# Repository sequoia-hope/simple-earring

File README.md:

# simple_earring

Co-designed LED earring: a Ø30.5 mm teardrop, 4-layer board with an RP2350A and external QSPI
flash in the middle and 45 RGB LEDs on two rings round it (37 on the outer ring, 8 inside). It runs
from a small LiPo cell (LPR302823) on the back and charges over USB-C. One button does both power
(a soft latch) and BOOTSEL. There is also an IMU, an ambient light sensor and a generated TPU clip-on
case. JLCPCB rules, all parts from LCSC.

The current board (rev 3, variant A) uses 45 WS2816C-1313 addressable pixels split into three
switched zones. Variants B–F study a cheaper build that drives plain RGB LEDs (XL-1615) from a
matrix driver (AW20198QNR), about $3 less per board. It routes on 6 layers; 4 layers is down to a few
open connections.

**Project page: <https://sequoia-hope.github.io/simple-earring/>**: every design variant (A, the
routed WS2816C board, and the B–F matrix-driver study) with board previews, a comparison table, the
interactive viewer (schematic, PCB layers, 3D) and the design notes. It is the local dashboard
(`proj up simple_earring`), published with `scripts/publish_pages.py --push`.

The design is *generated*: edit `design.yaml` (shape, LED count, sizes) and
`scripts/circuit.py` (netlist), then rebuild.

**Status:** rev 1 (SK6805-EC10 LEDs, 2032 coin cell) was ordered, assembled and works. It lives in a
separate worktree at `~/pcb/simple_earring_shipped` (commit `43eadc1`). This tree is rev 3: variant A
is routed with ultraroute to 0 DRC errors / 0 unconnected and has passed gate 7. The matrix variants
are placed; the 4- or 6-layer decision for them is open. See `docs/PLAN.md` for the plan of record
and the project page's feed for the narrative.

## Pipeline

```
python3 build.py                # full: board -> place -> route -> drc -> render -> export
python3 build.py --to place     # stop after a stage (board|place|route|drc|render|export)
```

Stages (each is also runnable standalone from `scripts/`):

| stage  | script              | what it does                                        |
|--------|---------------------|-----------------------------------------------------|
| board  | `gen_board.py`      | netlist from `circuit.py` -> fresh 4-layer .kicad_pcb, outline, nets |
| place  | `place.py`          | LED ring, MCU cluster front, holder back, USB at edge |
| route  | `route.py`          | locked pre-routes + pours, then ultraroute for the rest, zone fills |
| drc    | `drc.py`            | kicad-cli DRC, parsed pass/fail report              |
| render | `render.py`         | renders, layer PNGs, GLB, and the `out/` dashboard  |
| export | `export.py`         | JLCPCB gerbers/drill + BOM/CPL from LCSC numbers    |

The KiCad project is `hw/earring/a/earring.kicad_*` (the Boardroom suite's
`hw/<board>/<variant>/` layout; `scripts/paths.py` owns the locations). Build products
land in `out/` (renders, dashboard, `drc.json`, `production/`, `jlcpcb/`).

The dashboard's design gallery reads `design/variants.toml` (card text) and `pcbview.toml` (the
boards); rebuild the viewer with `scripts/view.sh build pcbview.toml`, rewrite the page with
`python3 scripts/render.py --index-only`, then publish it to GitHub Pages (the `gh-pages` branch)
with `python3 scripts/publish_pages.py --push`.

## Boardroom suite

This is a Boardroom project (`~/Software/easy_pcb`): `design/status.json` is its
headline state, `.claude/skills/pcb-design/` the vendored skill, `pcbview.toml` the
viewer config. `compose/earring/` is Circuit Composer's view of the circuit
(generated by `scripts/export_compose.py`, build stage `compose`), and
`route/earring/recipe.json` is the ultraroute recipe behind the installed route.
Routing is ultraroute: the `route` stage runs the pinned `vendor/ultraroute`
(`git submodule update --init`; `scripts/route.sh` builds it, needs Rust) with that recipe.
Alongside the board pipeline: `gen_schematic.py` (readable schematic + PDF),
`gen_case.py` (TPU case STLs/STEP), `firmware/` (PlatformIO, arduino-pico), and
`tools/` (bench instruments — charge monitor, placement spot scanner).

## Dashboard

```
cd out && python3 -m http.server 8618 --bind 0.0.0.0
```

`out/index.html` is a reverse-chronological update feed over the live build
outputs: renders, the copper-layer stack viewer, the 3D board, the schematic,
the case preview and the bench pages. It is **generated by `scripts/render.py`**
(the `FEED` list at the top of that file) — hand edits to the served page are
wiped by the next build. `python3 scripts/render.py --index-only` rewrites just
the page.

## Sources of truth

- `design.yaml` — geometry + rules parameters
- `scripts/circuit.py` — components and nets (references `bom/parts.yaml`)
- `bom/parts.yaml` — every part with LCSC number + footprint
- `library/parts.pretty/` — local footprints (proven ones lifted from prior boards)
- `docs/PLAN.md` — plan of record: current state, open work, hard-won constraints

## Provenance

Footprints and circuit patterns reuse the proven `earring` (RP2040 + LGS4056H + USB-C)
and `rp2350-pendant` (RP2350 QFN-60, 1010 LED ring) projects.

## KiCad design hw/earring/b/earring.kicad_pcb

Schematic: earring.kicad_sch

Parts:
BT1: LPR302823; BAT_LPR302823_PADS
C1, C2, C3, C4, C5, C6, C7, C8, C9, C21, C23, C24, C25, C26, C27, C28, C77, C81, C83, C85, C87: 100n; C_0402_1005Metric
C11, C12, C13, C22: 4.7u; C_0402_1005Metric_small_pads
C14, C15: 15p; C_0402_1005Metric
C16, C17, C29, C75, C86: 10u; C_0603_1608Metric
C18, C19, C80, C82, C84: 1u; C_0402_1005Metric
C76: 10n; C_0402_1005Metric
D2: BAV99W; SOT-323_BAT54SW
D3: 1N4007WS; D_SOD-323
D4: BAV70W; SOT-323_BAT54SW
D5: 1N4148WS; D_SOD-323
D6: PESD5V0S1BL; D_SOD-882
J1: USB-C; USB-C_SMD-TYPE-C-31-M-12_1
L1: 3.3uH; L_pol_2016
LED1, LED2, LED3, LED4, LED5, LED6, LED7, LED8, LED9, LED10, LED11, LED12, LED13, LED14, LED15, LED16, LED17, LED18, LED19, LED20, LED21, LED22, LED23, LED24, LED25, LED26, LED27, LED28, LED29, LED30, LED31, LED32, LED33, LED34, LED35, LED36, LED37, LED38, LED39, LED40, LED41, LED42, LED43, LED44, LED45: XL-1010RGB; LED_XL-1010RGB
Q1: ALS-PT19; SENSOR_ALS-PT19
Q2, Q8: CJ2101; SOT-323_MOSFET
Q4: LBSS84WT1G; SOT-323_MOSFET
Q5, Q6, Q7: BSS138W; SOT-323_MOSFET
R1, R3, R30: 1k; R_0402_1005Metric
R2, R19, R20, R22: 10k; R_0402_1005Metric
R4, R5: 5.1k; R_0402_1005Metric
R6, R7: 27; R_0402_1005Metric
R8: 18k; R_0402_1005Metric
R11, R12, R21, R29: 1M; R_0402_1005Metric
R13: 33; R_0402_1005Metric
R14, R15, R27, R38, R39: 4.7k; R_0402_1005Metric
R16: 22k; R_0402_1005Metric
R17, R18, R24, R25, R26, R36, R37: 100k; R_0402_1005Metric
R28: 680k; R_0402_1005Metric
R35: 47k; R_0402_1005Metric
SW2: PWR; SW_B3U-3000P
TP1: RUN; TestPoint_Pad_1.5x1.5mm
TP2: SWCLK; TestPoint_Pad_1.5x1.5mm
TP3: SWDIO; TestPoint_Pad_1.5x1.5mm
U1: RP2350A; RP2350-QFN-60-1EP_7x7_P0.4mm_EP3.4x3.4mm_ThermalVias
U2: LGS4056H; DFN-8-1EP_2x2mm_P0.5mm_EP0.9x1.5mm
U3: NCP730-3.3; WDFN-6-2x2
U5: USBLC6-2P6; SOT-666
U6: LSM6DS3TR-C; LGA-14_L3.0-W2.5-P0.50-TL
U7: W25Q16JVUXIQ; USON-8_L3.0-W2.0-P0.50-BL-EP
U8: 74LVC2G14; SOT-363_SC-70-6
U11: IS31FL3741A; QFN-60-1EP_7x7mm_P0.4mm_EP5.4x5.4mm
Y1: 12MHz; Crystal_SMD_3225-4Pin_3.2x2.5mm_ABM8

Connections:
3V3: C1.1, C2.1, C3.1, C4.1, C7.1, C8.1, C9.1, C11.1, C19.1, C23.1, C24.1, C25.1, C77.1, Q1.1 (C), Q8.2 (S), R2.2, R13.1, R14.2, R15.2, R26.1, R37.2, R38.2, R39.2, U1.1 (IOVDD), U1.11 (IOVDD), U1.20 (IOVDD), U1.30 (IOVDD), U1.38 (IOVDD), U1.44 (ADC_AVDD), U1.45 (IOVDD), U1.49 (VREG_VIN), U1.53 (USB_OTP_VDD), U1.54 (QSPI_IOVDD), U3.1 (OUT), U6.2 (SDx), U6.3 (SCx), U6.5 (VDDIO), U6.8 (VDD), U6.12 (CS), U7.8 (VCC), U8.5 (VCC)
BOOTSEL: R3.1, U1.60 (QSPI_SS), U7.1 (/CS)
BOOTSEL_SW: Q7.3 (D), R3.2
BOOT_TMR: C75.1, D5.2 (A), R28.2, U8.1 (1A)
BTN_EXT: D6.1, R30.1, SW2.2
BTN_N: C27.1, D4.3 (K), R30.2
BTN_SENSE: D5.1 (K), Q8.3 (D), R27.1, R28.1, U1.33 (GPIO21)
CC1: J1.A5 (CC1), R4.1
CC2: J1.B5 (CC2), R5.1
CHRG: U1.31 (GPIO19), U2.7 (CHRG)
CHRG_DONE: U1.42 (GPIO28), U2.6 (DONE)
CS1: LED1.1 (R), LED2.1 (R), LED3.1 (R), LED4.1 (R), LED5.1 (R), LED6.1 (R), LED7.1 (R), LED8.1 (R), LED9.1 (R), U11.26 (CS1)
CS2: LED1.2 (G), LED2.2 (G), LED3.2 (G), LED4.2 (G), LED5.2 (G), LED6.2 (G), LED7.2 (G), LED8.2 (G), LED9.2 (G), U11.27 (CS2)
CS3: LED1.4 (B), LED2.4 (B), LED3.4 (B), LED4.4 (B), LED5.4 (B), LED6.4 (B), LED7.4 (B), LED8.4 (B), LED9.4 (B), U11.28 (CS3)
CS4: LED10.1 (R), LED11.1 (R), LED12.1 (R), LED13.1 (R), LED14.1 (R), LED15.1 (R), LED16.1 (R), LED17.1 (R), LED18.1 (R), U11.29 (CS4)
CS5: LED10.2 (G), LED11.2 (G), LED12.2 (G), LED13.2 (G), LED14.2 (G), LED15.2 (G), LED16.2 (G), LED17.2 (G), LED18.2 (G), U11.30 (CS5)
CS6: LED10.4 (B), LED11.4 (B), LED12.4 (B), LED13.4 (B), LED14.4 (B), LED15.4 (B), LED16.4 (B), LED17.4 (B), LED18.4 (B), U11.31 (CS6)
CS7: LED19.1 (R), LED20.1 (R), LED21.1 (R), LED22.1 (R), LED23.1 (R), LED24.1 (R), LED25.1 (R), LED26.1 (R), LED27.1 (R), U11.32 (CS7)
CS8: LED19.2 (G), LED20.2 (G), LED21.2 (G), LED22.2 (G), LED23.2 (G), LED24.2 (G), LED25.2 (G), LED26.2 (G), LED27.2 (G), U11.33 (CS8)
CS9: LED19.4 (B), LED20.4 (B), LED21.4 (B), LED22.4 (B), LED23.4 (B), LED24.4 (B), LED25.4 (B), LED26.4 (B), LED27.4 (B), U11.34 (CS9)
CS10: LED28.1 (R), LED29.1 (R), LED30.1 (R), LED31.1 (R), LED32.1 (R), LED33.1 (R), LED34.1 (R), LED35.1 (R), LED36.1 (R), U11.35 (CS10)
CS11: LED28.2 (G), LED29.2 (G), LED30.2 (G), LED31.2 (G), LED32.2 (G), LED33.2 (G), LED34.2 (G), LED35.2 (G), LED36.2 (G), U11.37 (CS11)
CS12: LED28.4 (B), LED29.4 (B), LED30.4 (B), LED31.4 (B), LED32.4 (B), LED33.4 (B), LED34.4 (B), LED35.4 (B), LED36.4 (B), U11.38 (CS12)
CS13: LED37.1 (R), LED38.1 (R), LED39.1 (R), LED40.1 (R), LED41.1 (R), LED42.1 (R), LED43.1 (R), LED44.1 (R), LED45.1 (R), U11.39 (CS13)
CS14: LED37.2 (G), LED38.2 (G), LED39.2 (G), LED40.2 (G), LED41.2 (G), LED42.2 (G), LED43.2 (G), LED44.2 (G), LED45.2 (G), U11.40 (CS14)
CS15: LED37.4 (B), LED38.4 (B), LED39.4 (B), LED40.4 (B), LED41.4 (B), LED42.4 (B), LED43.4 (B), LED44.4 (B), LED45.4 (B), U11.41 (CS15)
DRV_INTB: R37.1, U1.3 (GPIO1), U11.7 (INTB)
DRV_ISET: R35.1, U11.13 (ISET)
DRV_SCL: R39.1, U1.28 (GPIO17), U11.10 (SCL)
DRV_SDA: R38.1, U1.27 (GPIO16), U11.9 (SDA)
DRV_SDB: C87.1, R36.1, U1.29 (GPIO18), U11.11 (SDB)
GND: BT1.2 (-), C1.2, C2.2, C3.2, C4.2, C5.2, C6.2, C7.2, C8.2, C9.2, C11.2, C12.2, C13.2, C14.2, C15.2, C16.2, C17.2, C18.2, C19.2, C21.2, C22.2, C23.2, C24.2, C25.2, C26.2, C27.2, C28.2, C29.2, C75.2, C77.2, C80.2, C81.2, C82.2, C83.2, C84.2, C85.2, C86.2, C87.2, D6.2, J1.1 (SHLD), J1.2 (SHLD), J1.3 (SHLD), J1.4 (SHLD), J1.A1B12 (GND), J1.B1A12 (GND), Q5.2 (S), Q6.2 (S), Q7.2 (S), R4.2, R5.2, R8.2, R12.2, R16.2, R17.2, R20.2, R21.2, R25.2, R27.2, R29.2, R35.2, R36.2, SW2.1, U1.47 (VREG_PGND), U1.61 (GND(EP)), U2.1 (TEMP), U2.3 (GND), U2.9 (GND(EP)), U3.3 (GND), U3.EP, U5.2 (GND), U6.1 (SDO/SA0), U6.6 (GND), U6.7 (GND), U7.4 (GND), U7.9 (GND(EP)), U8.2 (GND), U11.8 (ADDR), U11.12 (GND), U11.36 (GND), U11.55 (GND), U11.61 (GND(EP)), Y1.2, Y1.4
IMU_INT1: U1.12 (GPIO8), U6.4 (INT1)
IMU_SCL: R15.1, U1.15 (GPIO11), U6.13 (SCL)
IMU_SDA: R14.1, U1.9 (GPIO6), U6.14 (SDA)
LATCH_G: D4.2 (A2), Q4.1 (G), Q5.3 (D), R24.2
LIGHT: C26.1, Q1.2 (E), R16.1, U1.40 (GPIO26/ADC0)
LONG: C76.1, Q7.1 (G), U8.4 (2Y)
LONG_N: U8.3 (2A), U8.6 (1Y)
PATH_GATE: Q2.1 (G), R21.1, R22.2
PRESS_N: D4.1 (A1), Q8.1 (G), R26.2
PROG: R8.1, U2.2 (PROG)
PWR_EN: D2.3 (K1A2), R17.1, R18.2, U3.4 (EN)
PWR_HOLD: Q5.1 (G), R25.1, U1.32 (GPIO20)
QSPI_SCLK: U1.56 (QSPI_SCLK), U7.6 (CLK)
QSPI_SD0: U1.57 (QSPI_SD0), U7.5 (DI/IO0)
QSPI_SD1: U1.59 (QSPI_SD1), U7.2 (DO/IO1)
QSPI_SD2: U1.58 (QSPI_SD2), U7.3 (/WP/IO2)
QSPI_SD3: U1.55 (QSPI_SD3), U7.7 (/HOLD/IO3)
RUN: Q6.3 (D), R2.1, TP1.1, U1.26 (RUN)
RUN_KICK: C76.2, Q6.1 (G), R29.1
SW1: LED1.3 (A), LED10.3 (A), LED19.3 (A), LED28.3 (A), LED37.3 (A), U11.16 (SW1)
SW2: LED2.3 (A), LED11.3 (A), LED20.3 (A), LED29.3 (A), LED38.3 (A), U11.17 (SW2)
SW3: LED3.3 (A), LED12.3 (A), LED21.3 (A), LED30.3 (A), LED39.3 (A), U11.18 (SW3)
SW4: LED4.3 (A), LED13.3 (A), LED22.3 (A), LED31.3 (A), LED40.3 (A), U11.19 (SW4)
SW5: LED5.3 (A), LED14.3 (A), LED23.3 (A), LED32.3 (A), LED41.3 (A), U11.20 (SW5)
SW6: LED6.3 (A), LED15.3 (A), LED24.3 (A), LED33.3 (A), LED42.3 (A), U11.21 (SW6)
SW7: LED7.3 (A), LED16.3 (A), LED25.3 (A), LED34.3 (A), LED43.3 (A), U11.22 (SW7)
SW8: LED8.3 (A), LED17.3 (A), LED26.3 (A), LED35.3 (A), LED44.3 (A), U11.23 (SW8)
SW9: LED9.3 (A), LED18.3 (A), LED27.3 (A), LED36.3 (A), LED45.3 (A), U11.24 (SW9)
SWCLK: TP2.1, U1.24 (SWCLK)
SWDIO: TP3.1, U1.25 (SWDIO)
SW_ON: D2.1 (A1), Q4.3 (D), R11.1
USB_C_DN: J1.A7 (D-), J1.B7 (D-), R7.1, U5.3 (IO2), U5.4 (IO2)
USB_C_DP: J1.A6 (D+), J1.B6 (D+), R6.1, U5.1 (IO1), U5.6 (IO1)
USB_DM: R7.2, U1.51 (USB_DM)
USB_DP: R6.2, U1.52 (USB_DP)
VBATT: BT1.1 (+), C17.1, D2.2 (K2), Q2.3 (D), Q4.2 (S), R24.1, U2.5 (BAT)
VBSENSE: C21.1, R11.2, R12.1, U1.43 (GPIO29/ADC3)
VBUS: C16.1, C28.1, D3.2 (A), J1.A4B9 (VBUS), J1.B4A9 (VBUS), R18.1, R19.1, R22.1, U2.4 (VCC), U2.8 (CE), U5.5 (VBUS)
VBUS_SENSE: R19.2, R20.1, U1.41 (GPIO27)
VDD_CORE: C5.1, C6.1, C12.1, C13.1, L1.1, U1.6 (DVDD), U1.23 (DVDD), U1.39 (DVDD), U1.50 (VREG_FB)
VREG_AVDD: C22.1, R13.2, U1.46 (VREG_AVDD)
VREG_LX: L1.2, U1.48 (VREG_LX)
VSYS: C18.1, C29.1, C80.1, C81.1, C82.1, C83.1, C84.1, C85.1, C86.1, D3.1 (K), Q2.2 (S), U3.6 (IN), U11.14 (AVCC), U11.15 (PVCC), U11.25 (PVCC)
XIN: C14.1, U1.21 (XIN), Y1.1
XOUT: R1.2, U1.22 (XOUT)
XTAL_R: C15.1, R1.1, Y1.3

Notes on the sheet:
simple_earring — generated schematic
143 components / 78 nets / 4-layer JLCPCB stackup. Power rails (GND, 3V3, VBATT, VSYS, VLED, VBUS, VDD_CORE) are power symbols; only cross-block signals use global labels. Generated from scripts/circuit.py — do not hand-edit; rebuild with `python3 build.py --only schematic`.
J1 is a TYPE-C-31-M-12 right-angle receptacle. VBUS charges the cell AND (rev 2) runs
the board through D3 -> VSYS while a cable is in — see the power-path block.
USB-C receptacle / ESD / series R
CHRG / DONE are open-drain -> GPIO with internal pull-up (low = active); software owns the charge indicator.
Li-ion charger (LGS4056H, 50mA) + LPR302823 LiPo
1M:1M divider off SW_ON, the power latch's output
(VBATT while the latch is held or the button is
pressed). Latch ON: VBATT/2 battery telemetry. Latch
OFF + USB: reads 0, telling firmware to show charge
status instead of running the show. GPIO29/ADC3.
Latch / battery sense -> ADC
3V3 LDO — EN = power latch OR USB (diode-OR, clamped)
Rev 2: USB boots the board even with the latch off. Against
R17's pulldown EN sits at ~VBUS/2, and D2's second diode
clamps it to VBATT+Vf (NCP730 abs max V_EN is VIN+0.3, even
during precharge of a dead cell). Firmware then sees
SW_ON=0 on the sense divider and shows charge status
instead of running the show.
USB wake — VBUS feeds EN through R18
Press: BTN_N -> GND pulls LATCH_G low through D4 A2, Q4 turns on,
SW_ON = VBATT enables the LDO through D2. The CPU then drives
PWR_HOLD high so Q5 keeps LATCH_G low after release. Long press:
firmware drops PWR_HOLD and power falls when the button is
released. D4 A1 pulls PRESS_N low while pressed (the one-button
block turns that into BTN_SENSE). With the board off BTN_N sits
near VBATT and PRESS_N at 0V, so A1 is reverse-biased. D4 is
SILICON (BAV70W), not Schottky: the off-state leaks x R24 must
stay under Q4's 0.45V minimum threshold even hot. ESD: D6 clamps
a strike at the pad and R30 keeps it off BTN_N/D4; C27 debounces.
power button + soft latch
Hold the power button: BTN_SENSE goes high (Q8), C75 charges through R28 and U8 trips 2.2-10.3s later (5s typ; spread
is U8's VT+ and C75's X5R tolerance/bias, simulated in design/sim/button). LONG straps QSPI_SS low through Q7/R3 for as
long as the button is held and kicks RUN low for ~10ms (C76/R29 -> Q6): the chip resets into BOOTSEL. Flash is not
touched. On battery the reset drops PWR_HOLD, so the board turns off on release: the force-off for hung firmware. D5
empties C75 on release. Firmware: GPIO21 no pull-up, high = held; long-press-off < 2s.
one button: long hold = BOOTSEL / force-off
Rev 2: VBATT is the cell alone, VSYS runs the board, so the charger's whole 41mA reaches the cell in
either switch position. Q2's SOURCE is VSYS and its drain VBATT — a P-FET body diode conducts

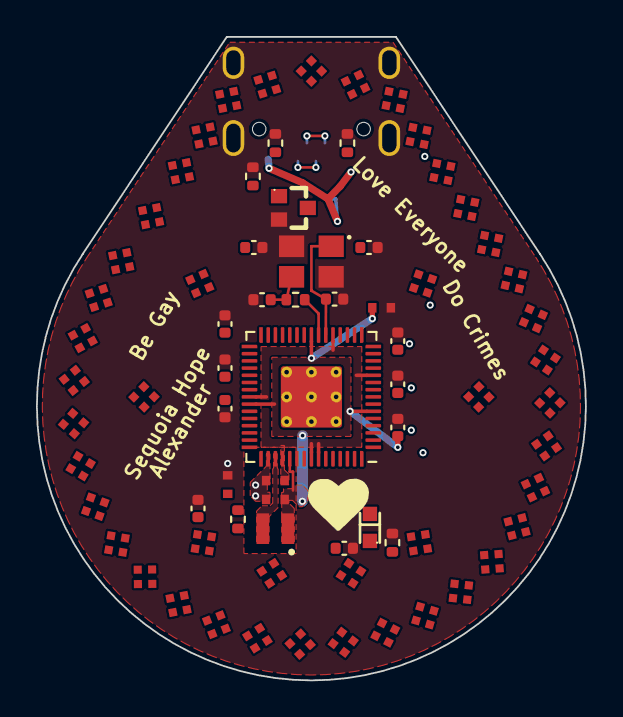
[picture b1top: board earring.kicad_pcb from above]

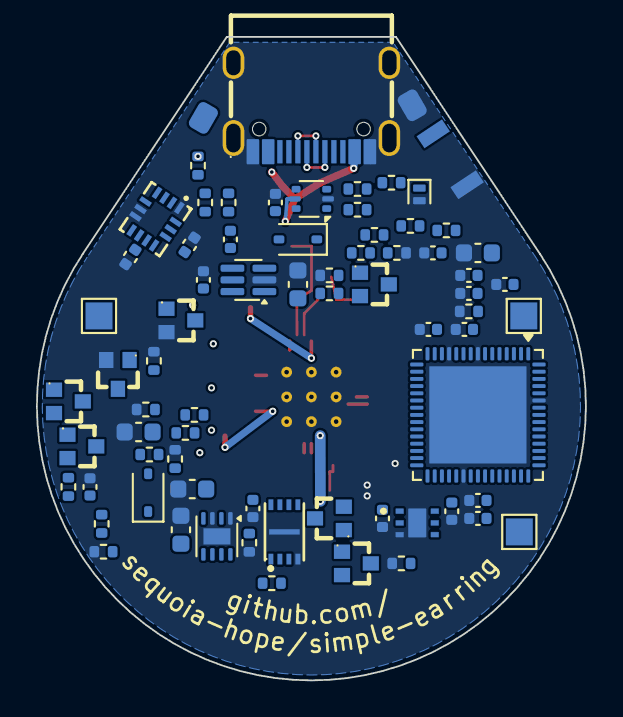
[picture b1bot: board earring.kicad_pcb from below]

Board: 6 copper layers, 30.5 x 35.8 mm, 143 parts (71 on the bottom side), 78 nets.

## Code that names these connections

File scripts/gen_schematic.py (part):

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        R = list(sides.get("r", []))
        T = list(sides.get("t", []))
        B = list(sides.get("b", []))
        # Top/bottom pin names run vertically INSIDE the box and would be
        # written straight through any side-pin name whose text reaches the
        # same columns. Where they would collide, reserve as many side slots
        # as the vertical name is tall so the two never share a row.
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            ys = [p[1] for p in pts]
            if max(ys) - min(ys) >= max(xs) - min(xs):
                # pins stack vertically -> park the text alongside the body,
                # between the two pins so it cannot reach either run
                rx, ry, rj = x + hw + 0.6, y - 2.0, "left bottom"
                vx, vy, vj = x + hw + 0.6, y + 1.1, "left bottom"
            else:
                # pins run left-right -> stack the text above and below,
                # stepped off the pin axis so it clears the wires' corners
                rx, ry, rj = x + 1.9, y - hh - 2.8, "left bottom"
                vx, vy, vj = x + 1.9, y + hh + 4.2, "left bottom"
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    def label(self, net, p, rot=0, just="left", size=1.0):
        """Name a wire that KiCad would otherwise auto-name.

        These are GLOBAL labels even though the run is local, because a
        plain label on the root sheet comes back out of the netlister as
        `/LED_D7`, and the board is matched to circuit.py by net name — a
        rename would relabel every net on a hand-routed board. Drawn small,
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# ---------------------------------------------------------------------------
def mcu_sides():
    gp = {g: p for g, p in GPIO.items()}
    used = {29: "GPIO18", 28: "GPIO17", 27: "GPIO16", 3: "GPIO1", 2: "GPIO0",
            34: "GPIO22", 9: "GPIO6", 15: "GPIO11", 12: "GPIO8",
            31: "GPIO19", 32: "GPIO20", 33: "GPIO21", 42: "GPIO28",
            40: "GPIO26/ADC0", 43: "GPIO29/ADC3"}
    unused = [(gp[g], f"GPIO{g}") for g in sorted(gp)
              if gp[g] not in used and gp[g] != 43]
    # Side pins are grouped by the block they wire to, with the gaps sized so
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            + [(21, "XIN"), (22, "XOUT")]
            + [None] * 8
            + [(51, "USB_DM"), (52, "USB_DP")])
    right = [(29, "GPIO18"), (28, "GPIO17"), (27, "GPIO16"), (3, "GPIO1"),
             (2, "GPIO0"), (34, "GPIO22"), (9, "GPIO6"), (15, "GPIO11"),
             (12, "GPIO8"), (31, "GPIO19"), (32, "GPIO20"), (33, "GPIO21"),
             (42, "GPIO28"),
             (40, "GPIO26/ADC0"), (43, "GPIO29/ADC3")]
    top = [(1, "IOVDD"), (11, "IOVDD"), (20, "IOVDD"), (30, "IOVDD"),
           (38, "IOVDD"), (45, "IOVDD"), (54, "QSPI_IOVDD"),
           (53, "USB_OTP_VDD"), (44, "ADC_AVDD"), None,
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    "rgb_led_1615": {"t": [("2", "A")],
                     "b": [("1", "R"), ("3", "G"), ("4", "B")]},
    # 74LVC2G14 (U8): 1A -> 1Y feeds 2A -> 2Y. 1Y and 2A sit next to each
    # other on the right so the LONG_N link is a two-pin bracket, and 2Y
    # leaves below it.
    "logic_schmitt2": {"l": [("1", "1A"), None, None, None],
                       "r": [("6", "1Y"), ("3", "2A"), None, ("4", "2Y")],
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    bk.take("U2", "2", "PROG")
    xp = u["2"][0] - 20.32
    s.wire(u["2"], (xp, u["2"][1]))
    s.label("PROG", (xp + 3.81, u["2"][1]), size=1.0)
    s.wire((xp, u["2"][1]), (xp, u["2"][1] + 5.08))
    vdrop(s, cir, bk, "R8", xp, u["2"][1] + 5.08, "GND")
    # TEMP grounded (NTC disabled)
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        bk.take("U2", p, net)
        s.wire(u[p], (u[p][0] + 3.81, u[p][1]))
        s.glabel(net, (u[p][0] + 3.81, u[p][1]))
    s.note("CHRG / DONE are open-drain -> GPIO with internal pull-up "
           "(low = active); software owns the charge indicator.",
           x - 40.64, u["3"][1] + 20.32, 115.0)
    s.end()
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
def blk_sense(s, cir, bk, x, y):
    s.begin("Latch / battery sense -> ADC")
    s.glabel("SW_ON", (x - 10.16, y), rot=180, just="right")
    s.wire((x - 10.16, y), (x, y))
    s.wire((x, y), (x, y + 3.81))
    r11 = put(s, cir, "R11", x, y + 7.62)
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    vdrop(s, cir, bk, "C21", x + 15.24, node[1], "GND")
    s.junction((x + 15.24, node[1]))
    s.wire(node, (x - 10.16, node[1]))
    s.glabel("VBSENSE", (x - 10.16, node[1]), rot=180, just="right")
    s.note("1M:1M divider off SW_ON, the power latch's output (VBATT "
           "while the latch is held or the button is pressed). Latch ON: "
           "VBATT/2 battery telemetry. Latch OFF + USB: reads 0, telling "
           "firmware to show charge status instead of running the show. "
           "GPIO29/ADC3.",
           x - 22.86, r12["2"][1] + 12.7, 56.0)
    s.end()

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    s.rail("GND", (u["3"][0], u["3"][1] + 6.35))
    # EN = SW_ON OR VBUS. D2 (BAT54SW series pair) stands VERTICALLY
    # beside U3 — the strip further left belongs to C18 and the IN
    # riser. SW_ON enters pin 1 from below, the clamp cathode (pin 2)
    # rises to VBATT above, and the midpoint (pin 3) taps right, in
    # line with U3's EN pin. Diode 1 lifts EN to VBATT-0.2 when the
    # switch is on; diode 2 clamps EN to VBATT+Vf because NCP730 abs
    # max V_EN is only (V_IN + 0.3). The VBUS half of the OR (R18) has
    # its own block — see "USB wake"; the nets meet on the PWR_EN
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    s.wire(d2["3"], u4)
    # R17 pulldown hangs off the EN run (100k: EN has an internal <=1uA
    # pull-up to VIN, so a 1M pulldown could fail to turn the LDO off);
    # the PWR_EN glabel stubs off R17's riser
    s.junction((u4[0] - 6.35, u4[1]))
    s.wire((u4[0] - 6.35, u4[1]), (u4[0] - 6.35, u4[1] + 2.54))
    # drop=6.35 + the one-step-left column push the GND rail's text
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    vdrop(s, cir, bk, "R17", u4[0] - 6.35, u4[1] + 2.54, "GND", drop=6.35)
    s.junction((u4[0] - 6.35, u4[1] + 1.27))
    s.wire((u4[0] - 6.35, u4[1] + 1.27), (u4[0] - 7.62, u4[1] + 1.27))
    s.glabel("PWR_EN", (u4[0] - 7.62, u4[1] + 1.27), rot=180,
             just="right", size=1.0)
    # SW_ON (VBATT while the power latch is on) arrives from the latch
    # block on a global label — it was the slide switch's common until the
    # LiPo change, and D2 / R11 still read it exactly the same way
    s.path(d2["1"], (d2["1"][0], d2["1"][1] + 5.08),
           (d2["1"][0] - 10.16, d2["1"][1] + 5.08))
    s.glabel("SW_ON", (d2["1"][0] - 10.16, d2["1"][1] + 5.08), rot=180,
             just="right", size=1.0)
    s.end()

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    s.wire(q4["2"], (xs, y - 12.7))
    s.rail("VBATT", (xs, y - 12.7))
    s.path(q4["3"], (xs, y + 12.7), (xs + 12.7, y + 12.7))
    s.glabel("SW_ON", (xs + 12.7, y + 12.7), size=1.0)
    # LATCH_G bus, Q4 gate leftwards
    xr, xq, xe = x - 12.7, x - 17.78, x - 27.94
    s.wire(q4["1"], (xe, y))
    s.label("LATCH_G", (xe + 1.27, y), size=1.0)
    r24 = put(s, cir, "R24", xr, y - 7.62)
    bk.take("R24", "1", "VBATT")
    bk.take("R24", "2", "LATCH_G")
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    s.wire(r25["1"], (xpd, y + 35.56))
    s.wire(r25["2"], (xpd, y + 50.8))
    s.rail("GND", (xpd, y + 50.8))
    s.glabel("PWR_HOLD", (xpd - 2.54, y + 35.56), rot=180, just="right")
    # D4 at the bus's far end: A2 = LATCH_G (right), A1 = BTN_SENSE (left),
    # K = BTN_N down into the button, which closes to GND
    # ref/value parked ABOVE the bus: below it they land on the BTN_N run
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    bk.take("D4", "2", "LATCH_G")
    bk.take("D4", "3", "BTN_N")
    s.wire(d4["1"], (d4["1"][0] - 5.08, y))
    s.glabel("PRESS_N", (d4["1"][0] - 5.08, y), rot=180, just="right")
    kx = d4["3"][0]
    s.wire(d4["3"], (kx, y + 12.7))
    s.label("BTN_N", (kx, y + 10.16), size=1.0)
    # R30 isolates BTN_N from the pad; D6 clamps at the pad
    r30 = put(s, cir, "R30", kx - 10.16, y + 12.7, rot=90)
    bk.take("R30", "1", "BTN_EXT")
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    bk.take("SW2", "1", "GND")
    bk.take("SW2", "2", "BTN_EXT")
    s.wire(sw["2"], (xx, y + 12.7))
    s.label("BTN_EXT", (xx, y + 15.24), size=1.0)
    s.wire(sw["1"], (sw["1"][0] - 2.54, y + 12.7))
    s.wire((sw["1"][0] - 2.54, y + 12.7), (sw["1"][0] - 2.54, y + 16.51))
    s.rail("GND", (sw["1"][0] - 2.54, y + 16.51))
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    s.rail("3V3", (q8["2"][0], y - 12.7))
    xg = x - 12.7
    s.wire(q8["1"], (xg - 7.62, y))
    s.glabel("PRESS_N", (xg - 7.62, y), rot=180, just="right")
    r26 = put(s, cir, "R26", xg, y - 3.81)
    bk.take("R26", "1", "3V3")
    bk.take("R26", "2", "PRESS_N")
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    s.wire(q8["3"], (xd, yb))
    s.junction((xd, yb))
    s.wire((xd, yb), (xg - 7.62, yb))
    s.glabel("BTN_SENSE", (xg - 7.62, yb), rot=180, just="right")
    s.junction((x - 5.08, yb))
    vdrop(s, cir, bk, "R27", x - 5.08, yb, "GND")
    # R28 (timer) and D5 (reset on release) in parallel to BOOT_TMR
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    s.path((xa, yb), (xa, yd), d5["1"])
    s.path(d5["2"], (xt, yd), (xt, yb))
    s.junction((xt, yb))
    s.label("BOOT_TMR", (xt + 1.27, yb), size=1.0)
    xc = xt + 15.24
    s.junction((xc, yb))
    vdrop(s, cir, bk, "C75", xc, yb, "GND")
    # U8, pin 1 on the BOOT_TMR wire
    sx, sy = xf(*s.defs["logic_schmitt2"].pins["1"], 0)
    u8 = put(s, cir, "U8", xc + 10.16 - sx, yb - sy)
    bk.take("U8", "1", "BOOT_TMR")
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    bk.take("U8", "6", "LONG_N")
    bk.take("U8", "3", "LONG_N")
    xbk = u8["6"][0] + 10.16
    s.label("LONG_N", (u8["6"][0] + 1.27, u8["6"][1]), size=1.0)
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
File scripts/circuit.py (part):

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# GPIO roles
# LED ring: three zones since 2026-10-24 (left / right / centre), each its
# own chain, load switch and level shifter, so a dark zone draws nothing.
# The three data pins are ADJACENT (GPIO16-18, pins 27-29, top-left after
# the MCU rotation, next to the zones' entry LEDs), so one PIO program can
# clock all three chains in parallel from consecutive pins.
GP_LED_DATA_C = 16  # pin 27 -> Q10 -> centre zone (LED38..45)
GP_LED_DATA_R = 17  # pin 28 -> Q9  -> right zone (LED37 -> LED19, reversed)
GP_LED_EN_R = 0     # pin 2, next to LED_EN_L's pin 3 -> U9 ON
GP_LED_EN_C = 22    # pin 34, west-column run after BTN_SENSE -> U10 ON
GP_LED_DATA = 18  # pin 29: lands top-left after the 180deg MCU rotation,
                  # right next to LED1 at the start of the ring
GP_LED_EN = 1     # -> U4 (left zone) ON
ADC_VBSENSE = 43  # GPIO29_ADC3 pin number
ADC_LIGHT = 40    # GPIO26_ADC0 pin number: ambient light sensor (rev 2)
ADC_VBUS = 41     # GPIO27_ADC1 pin number: USB cable present (rev 3)
# IMU on I2C1 + INT1: all on the chip's right side after the 180deg
# rotation, facing the IMU's back-east spot. The exact GPIOs are picked so
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GP_I2C_SDA = 6    # I2C1 SDA, pin 9  (middle decap gap)
GP_I2C_SCL = 11   # I2C1 SCL, pin 15 (south passage below C2)
GP_IMU_INT1 = 8   # pin 12           (lower decap gap)
# Charger status: LGS4056H CHRG/DONE are open-drain -> GPIOs, read with
# internal pull-ups (low = active). The charge LED (old D1/R9) is gone —
# status is displayed in software.
# BOTH exit the WEST column and cross to U2 on In3 with committed vias
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# routed, but pushed the east half over capacity — 29 attempts across 7
# builds always stranded one east net: SWCLK/IMU_SDA/IMU_INT1/USB_DM
# rotating by seed); pin 4 behind C6 can't escape at all.
# CHRG = GPIO19 (pin 31): west column SOUTH end — pins 31-36 are all
# unused, so the lane past their tips down around C1's south corner is
# private. In3 via (-4.6,-5.8), landing via-in-pad in U2 pad 7. (Trying
# to pair CHRG through the same C5/C22 window as CHRG_DONE jammed it:
# two committed via discs walled the window mouth and the pad-tip
# corridor is single-lane past pin 42 — CHRG_DONE/VBSENSE/USB_DP all
# stranded, 5-unc plateau.)
# CHRG_DONE = GPIO28 (pin 42): straight west out the window (only
# VBSENSE shares it), In3 vias (-4.6,1.35) -> (7.8,6.6) NE of U2/C16.
GP_CHRG = 19      # pin 31: low while charging
# Power latch (LiPo change, 2026-10-22): the slide switch became a momentary
# button, so the CPU holds its own power on. Both take the unused west-column
# run after CHRG (pins 32-37 were all NC); the back interior they escape into
# is open now that BT1's Ø8 centre pad is gone. design/decisions.md.
GP_PWR_HOLD = 20  # pin 32: high = keep the LDO enabled (-> Q5 gate)
GP_BTN_SENSE = 21 # pin 33: power button held, ACTIVE HIGH (Q8 drives it,
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    for name in ("QSPI_SD0", "QSPI_SD1", "QSPI_SD2", "QSPI_SD3",
                 "QSPI_SCLK"):
        u1[RP_PINS[name]] = name
    u1[RP_PINS["XIN"]] = "XIN"
    u1[RP_PINS["XOUT"]] = "XOUT"
    u1[RP_PINS["SWCLK"]] = "SWCLK"
    u1[RP_PINS["SWD"]] = "SWDIO"
    u1[RP_PINS["RUN"]] = "RUN"
    u1[RP_PINS["ADC_AVDD"]] = "3V3"
    u1[RP_PINS["VREG_AVDD"]] = "VREG_AVDD"  # noise-sensitive: RC-filtered 3V3
    u1[RP_PINS["VREG_PGND"]] = "GND"
    u1[RP_PINS["VREG_LX"]] = "VREG_LX"
    u1[RP_PINS["VREG_VIN"]] = "3V3"
    u1[RP_PINS["VREG_FB"]] = "VDD_CORE"
    u1[RP_PINS["USB_DM"]] = "USB_DM"
    u1[RP_PINS["USB_DP"]] = "USB_DP"
    u1[RP_PINS["USB_OTP_VDD"]] = "3V3"
    u1[RP_PINS["QSPI_IOVDD"]] = "3V3"
    u1[RP_PINS["QSPI_SS"]] = "BOOTSEL"
    u1[RP_PINS["GND"]] = "GND"
    if matrix:
        # Variant B: the driver takes I2C0 on the old LED_DATA_C/R pins
        # (GPIO16 = I2C0 SDA, GPIO17 = I2C0 SCL, adjacent pins 27/28), SDB on
        # LED_DATA_L's GPIO18 and INTB on LED_EN_L's GPIO1. GPIO0 and GPIO22
        # (LED_EN_R/C) come free.
        u1[GPIO[GP_LED_DATA_C]] = "DRV_SDA"
        u1[GPIO[GP_LED_DATA_R]] = "DRV_SCL"
        if matrix_driver(design)["value"] == "AW20198QNR":
            u1[GPIO[GP_LED_DATA]] = "DRV_EN"   # no INTB: GPIO1 comes free
        else:
            u1[GPIO[GP_LED_DATA]] = "DRV_SDB"
            u1[GPIO[GP_LED_EN]] = "DRV_INTB"
    else:
        u1[GPIO[GP_LED_DATA]] = "LED_DATA_L"  # -> Q3 gate, NOT the ring directly
        u1[GPIO[GP_LED_DATA_R]] = "LED_DATA_R"
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    u1[ADC_VBSENSE] = "VBSENSE"
    u1[ADC_LIGHT] = "LIGHT"
    u1[ADC_VBUS] = "VBUS_SENSE"
    u1[GPIO[GP_I2C_SDA]] = "IMU_SDA"
    u1[GPIO[GP_I2C_SCL]] = "IMU_SCL"
    u1[GPIO[GP_IMU_INT1]] = "IMU_INT1"
    u1[GPIO[GP_CHRG]] = "CHRG"
    u1[GPIO[GP_CHRG_DONE]] = "CHRG_DONE"
    u1[GPIO[GP_PWR_HOLD]] = "PWR_HOLD"
    u1[GPIO[GP_BTN_SENSE]] = "BTN_SENSE"
    for p in GPIO.values():
        u1.setdefault(p, "")  # unused GPIOs NC
    c.add("U1", "mcu", "RP2350A", u1)
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    c.add("R13", "r_33", "33", {1: "3V3", 2: "VREG_AVDD"})
    c.add("C22", "c_4u7", "4.7u", {1: "VREG_AVDD", 2: "GND"})

    # --- crystal: XIN direct, XOUT via 1k; 2520-4P pins 1/3 xtal, 2/4 GND ---
    c.add("Y1", "crystal", "12MHz", {1: "XIN", 2: "GND", 3: "XTAL_R", 4: "GND"})
    c.add("R1", "r_1k", "1k", {1: "XTAL_R", 2: "XOUT"})
    c.add("C14", "c_15p", "15p", {1: "XIN", 2: "GND"})
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        5: "VBUS", 2: "GND",
    })
    # ST's USBLC6-2 ds §3: the rail-to-rail clamp only works if VBUS is a
    # stiff reference during the surge, so where the run from the VBUS pin
    # to +VCC cannot be kept short they ask for a 100nF right at the part.
    # Our only VBUS bulk (C16) sits over at the charger, so add a local one.
    c.add("C28", "c_100n", "100n", {1: "VBUS", 2: "GND"})
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        3: "GND",
        4: "VBUS",       # VCC
        5: "VBATT",      # BAT
        6: "CHRG_DONE",  # DONE open-drain -> GPIO28 (low = charge complete)
        7: "CHRG",       # CHRG open-drain -> GPIO19 (low = charging)
        8: "VBUS",       # CE high = enabled
        9: "GND",        # EP
    })
    c.add("R8", "r_18k", rprog_val, {1: "PROG", 2: "GND"})
    c.add("C16", "c_10u_0603", "10u", {1: "VBUS", 2: "GND"})
    c.add("C17", "c_10u_0603", "10u", {1: "VBATT", 2: "GND"})
    # (no charge LED: CHRG/DONE go straight to GPIOs with internal
    # pull-ups; software owns the charge indication)

    # --- battery ---
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    #   VBUS --|>|-- VSYS      D3, blocking SILICON rectifier (~0.8V; see D3)
    #   VBATT --Q2-- VSYS      P-FET, ON only when no cable is present
    #   VSYS  -> U3 (LDO IN), U4 (LED load switch IN)
    #   VBATT -> U2 pin 5 (charger BAT), BT1, C17, SW2  [cell node ONLY]
    #
    # Q2 ORIENTATION: source = VSYS, drain = VBATT. A P-FET's body diode
    # conducts drain->source, so this way it points cell->VSYS: it BLOCKS
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    #
    # COST: VSYS is ~4.7V, and SK6805 VIH = 0.7*VDD = 3.29V there (3.5V at
    # a 5.25V port) — above what a 3.3V IOVDD pad can drive. That is what
    # Q3/R23 down in the LED section are for. Diode-dropping VSYS into the
    # LED's window instead does NOT work: two Schottkys land at 4.3V typ
    # but 3.8V at the low corner (under the 3.7V floor) and 4.65V at the
    # high one (VIH 3.26V, still failing) — the window is narrower than
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    # R18. Blocking it would cost a third diode for zero benefit.)
    # (Rev-2 power path: IN is VSYS now, not VBATT. The D2 clamp still
    # references VBATT and is still legal — V_EN max is V_IN + 0.3 and
    # VSYS >= VBATT in every state, so clamping to the LOWER of the two is
    # conservative. NCP730 is a 38V-input part, so the 4.7V USB rail is a
    # non-event for it; it just drops 1.4V instead of 0.3V at ~20mA.)
    c.add("U3", "ldo", "NCP730-3.3", {
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    # tempco and the subthreshold current R17 turns into EN volts.
    # BAV70W at 4V/85C is ~1uA -> 0.1V. Gate-1/latch review,
    # design/gates/phase2.md; adoption review F2, design/gates/phase8.md.
    # (D4 A1 now drives PRESS_N, not the GPIO: the one-button block.)
    # R24 stays 100k (42uA while on). D6 (TVS) adds <=100nA at 25C (ds
    # IRM max at 5V; ~1uA hot by its Fig. 6) — simulated, design/sim/button.
    # USB still enables the LDO through R18 whatever the latch says.
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    #            pressed. 0V when the board is off, so D4 A1 is reverse-biased
    #            exactly as when it went to the GPIO pad: the off-state leak
    #            budget on LATCH_G is unchanged.
    #   Q8       P-FET inverter from 3V3: BTN_SENSE (GPIO21) becomes a clean
    #            active-high 0/3.3V "held". A P-FET because the 0.45V diode-OR
    #            low is too close to a Schmitt's VT- (0.6V min), but is 2.85V
    #            of gate drive against CJ2101's -0.45..-1V threshold.
    #   R27 4.7k BTN_SENSE pull-down. Firmware that still enables GPIO21's
    #            internal pull-up (32-86k) then holds the node at <=0.42V;
    #            add U8's input leak at its +1uA spec max x R28 (0.68V) and
    #            BOOT_TMR is still 1.1V, under VT+ min (1.42V at 3.3V), so
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    #
    # THE POWER PATH DOES NOT TOUCH THIS, deliberately: SW2 pin 1 stays on
    # VBATT (the cell), never VSYS. Wire it to VSYS and the reading becomes
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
